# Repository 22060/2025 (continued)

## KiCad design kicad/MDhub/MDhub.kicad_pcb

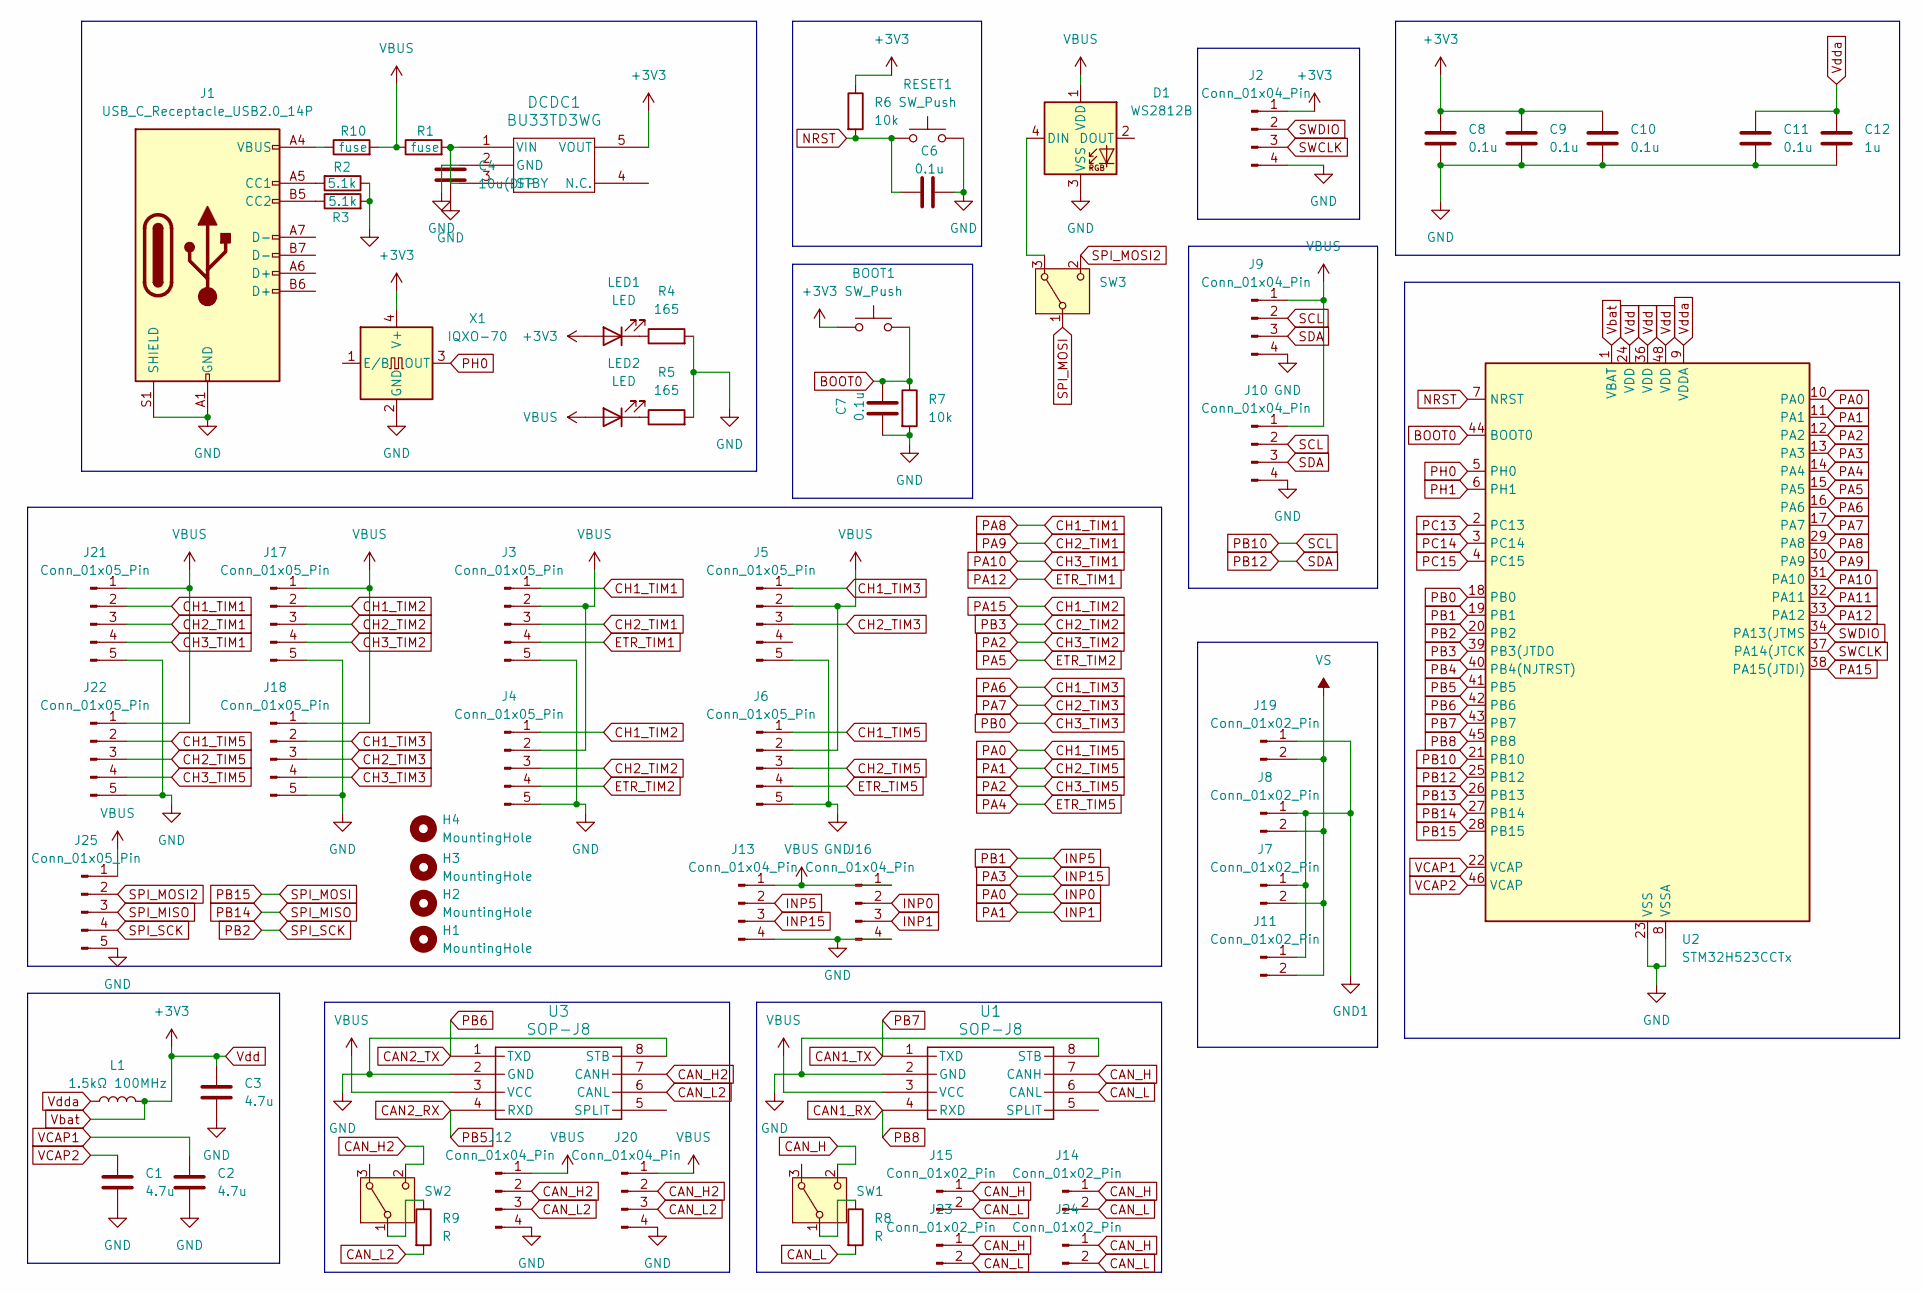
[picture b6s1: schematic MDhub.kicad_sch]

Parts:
BOOT1: SW_Push; SW_Tactile_SPST_NO_Straight_CK_PTS636Sx25SMTRLFS
C1, C2, C3: 4.7u; C_0603_1608Metric
C4: 10u(DFP; C_0603_1608Metric
C6, C7, C8, C9, C10, C11: 0.1u; C_0603_1608Metric
C12: 1u; C_0603_1608Metric
D1: WS2812B; LED_WS2812B_PLCC4_5.0x5.0mm_P3.2mm
DCDC1: BU33TD3WG; SSOP5
H1, H2, H3, H4: MountingHole; MountingHole_3.2mm_M3
J1: USB_C_Receptacle_USB2.0_14P; USB_C_Receptacle_aitendo
J2, J9, J10: Conn_01x04_Pin; Molex_KK-254_AE-6410-04A_1x04_P2.54mm_Vertical
J3, J4, J5, J6, J17, J18, J21, J22, J25: Conn_01x05_Pin; Molex_KK-254_AE-6410-05A_1x05_P2.54mm_Vertical
J7, J8: Conn_01x02_Pin; AMASS_XT60-F_1x02_P7.20mm_Vertical
J11, J19: Conn_01x02_Pin; AMASS_XT30PW-M_1x02_P2.50mm_Horizontal+3D
J12, J20: Conn_01x04_Pin; PinHeader_1x04_P2.54mm_Horizontal
J13, J16: Conn_01x04_Pin; Hirose_DF13-04P-1.25DSA_1x04_P1.25mm_Vertical
J14, J15, J23, J24: Conn_01x02_Pin; Hirose_DF13-02P-1.25DS_1x02_P1.25mm_Horizontal
L1: 1.5kΩ 100MHz; L_0805_2012Metric_Pad1.05x1.20mm_HandSolder
LED1, LED2: LED; LED_0603_1608Metric_Pad1.05x0.95mm_HandSolder
R1, R10: fuse; R_0603_1608Metric_Pad0.98x0.95mm_HandSolder
R2, R3: 5.1k; R_0603_1608Metric_Pad0.98x0.95mm_HandSolder
R4, R5: 165; R_0603_1608Metric_Pad0.98x0.95mm_HandSolder
R6, R7: 10k; R_0603_1608Metric_Pad0.98x0.95mm_HandSolder
R8, R9: R; R_0603_1608Metric_Pad0.98x0.95mm_HandSolder
RESET1: SW_Push; SW_Tactile_SPST_NO_Straight_CK_PTS636Sx25SMTRLFS
SW1, SW2, SW3: SW_Wuerth_450301014042; SW_Slide-03_Wuerth-WS-SLTV_10x2.5x6.4_P2.54mm
U1, U3: SOP-J8
U2: STM32H523CCTx; LQFP-48_7x7mm_P0.5mm
X1: IQXO-70; Oscillator_SMD_IQD_IQXO70-4Pin_7.5x5.0mm

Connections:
BOOT0: BOOT1.2, C7.2, R7.1, U2.44 (BOOT0)
CAN1_RX: U1.4 (RXD), U2.45 (PB8)
CAN1_TX: U1.1 (TXD), U2.43 (PB7)
CAN2_RX: U2.41 (PB5), U3.4 (RXD)
CAN2_TX: U2.42 (PB6), U3.1 (TXD)
CAN_H: J14.1, J15.1, J23.1, J24.1, SW1.2 (C), U1.7 (CANH)
CAN_H2: J12.2, J20.2, SW2.2 (C), U3.7 (CANH)
CAN_L: J14.2, J15.2, J23.2, J24.2, R8.2, U1.6 (CANL)
CAN_L2: J12.3, J20.3, R9.2, U3.6 (CANL)
CH1_TIM1: J3.1, J21.2, U2.29 (PA8)
CH1_TIM2: J4.1, J17.2, U2.38 (PA15(JTDI))
CH1_TIM3: J5.1, J18.2, U2.16 (PA6)
CH1_TIM5: J6.1, J16.2, J22.2, U2.10 (PA0)
CH2_TIM1: J3.3, J21.3, U2.30 (PA9)
CH2_TIM2: J4.3, J17.3, U2.39 (PB3(JTDO)
CH2_TIM3: J5.3, J18.3, U2.17 (PA7)
CH2_TIM5: J6.3, J16.3, J22.3, U2.11 (PA1)
CH3_TIM1: J21.4, U2.31 (PA10)
CH3_TIM2: J17.4, J22.4, U2.12 (PA2)
CH3_TIM3: J18.4, U2.18 (PB0)
ETR_TIM1: J3.4, U2.33 (PA12)
ETR_TIM2: J4.4, U2.15 (PA5)
ETR_TIM5: J6.4, U2.14 (PA4)
GND: C1.2, C2.2, C3.2, C4.2, C6.2, C7.1, C8.2, C9.2, C10.2, C11.2, C12.2, D1.3 (VSS), DCDC1.2 (GND), J1.A1 (GND), J1.A12 (GND), J1.B1 (GND), J1.B12 (GND), J1.S1 (SHIELD), J2.4, J3.5, J4.5, J5.5, J6.5, J9.4, J10.4, J12.4, J13.4, J16.4, J17.5, J18.5, J20.4, J21.5, J22.5, J25.5, R2.1, R3.2, R4.2, R5.2, R7.2, RESET1.2, U1.2 (GND), U1.8 (STB), U2.8 (VSSA), U2.23 (VSS), U2.35 (VSS), U2.47 (VSS), U3.2 (GND), U3.8 (STB), X1.2 (GND)
GND1: J7.1, J8.1, J11.1, J19.1
INP5: J13.2, U2.19 (PB1)
INP15: J13.3, U2.13 (PA3)
NRST: C6.1, R6.2, RESET1.1, U2.7 (NRST)
unnamed: D1.4 (DIN), SW3.3 (A)
unnamed: C4.1, DCDC1.1 (VIN), DCDC1.3 (STBY), R1.2
unnamed: J1.A5 (CC1), R2.2
unnamed: J1.B5 (CC2), R3.1
unnamed: J1.A4 (VBUS), J1.A9 (VBUS), J1.B4 (VBUS), J1.B9 (VBUS), R10.1
unnamed: LED1.1 (K), R4.1
unnamed: LED2.1 (K), R5.1
unnamed: R8.1, SW1.1 (B)
unnamed: R9.1, SW2.1 (B)
PA11: U2.32 (PA11)
PB2: J25.4, U2.20 (PB2)
PB4: U2.40 (PB4(NJTRST))
PB10: J9.2, J10.2, U2.21 (PB10)
PB12: J9.3, J10.3, U2.25 (PB12)
PB13: U2.26 (PB13)
PB14: J25.3, U2.27 (PB14)
PB15: SW3.1 (B), U2.28 (PB15)
PC13: U2.2 (PC13)
PC14: U2.3 (PC14)
PC15: U2.4 (PC15)
PH0: U2.5 (PH0), X1.3 (OUT)
PH1: U2.6 (PH1)
SPI_MOSI2: J25.2, SW3.2 (C)
SWCLK: J2.3, U2.37 (PA14(JTCK)
SWDIO: J2.2, U2.34 (PA13(JTMS)
VBUS: D1.1 (VDD), J3.2, J4.2, J5.2, J6.2, J9.1, J10.1, J12.1, J13.1, J16.1, J17.1, J18.1, J20.1, J21.1, J22.1, J25.1, LED2.2 (A), R1.1, R10.2, U1.3 (VCC), U3.3 (VCC)
VCAP1: C2.1, U2.22 (VCAP)
VCAP2: C1.1, U2.46 (VCAP)
VS: J7.2, J8.2, J11.2, J19.2
Vbat: BOOT1.1, C3.1, C8.1, C9.1, C10.1, DCDC1.5 (VOUT), J2.1, L1.2, LED1.2 (A), R6.1, U2.1 (VBAT), U2.24 (VDD), U2.36 (VDD), U2.48 (VDD), X1.4 (V+)
Vdda: C11.1, C12.1, L1.1, U2.9 (VDDA)

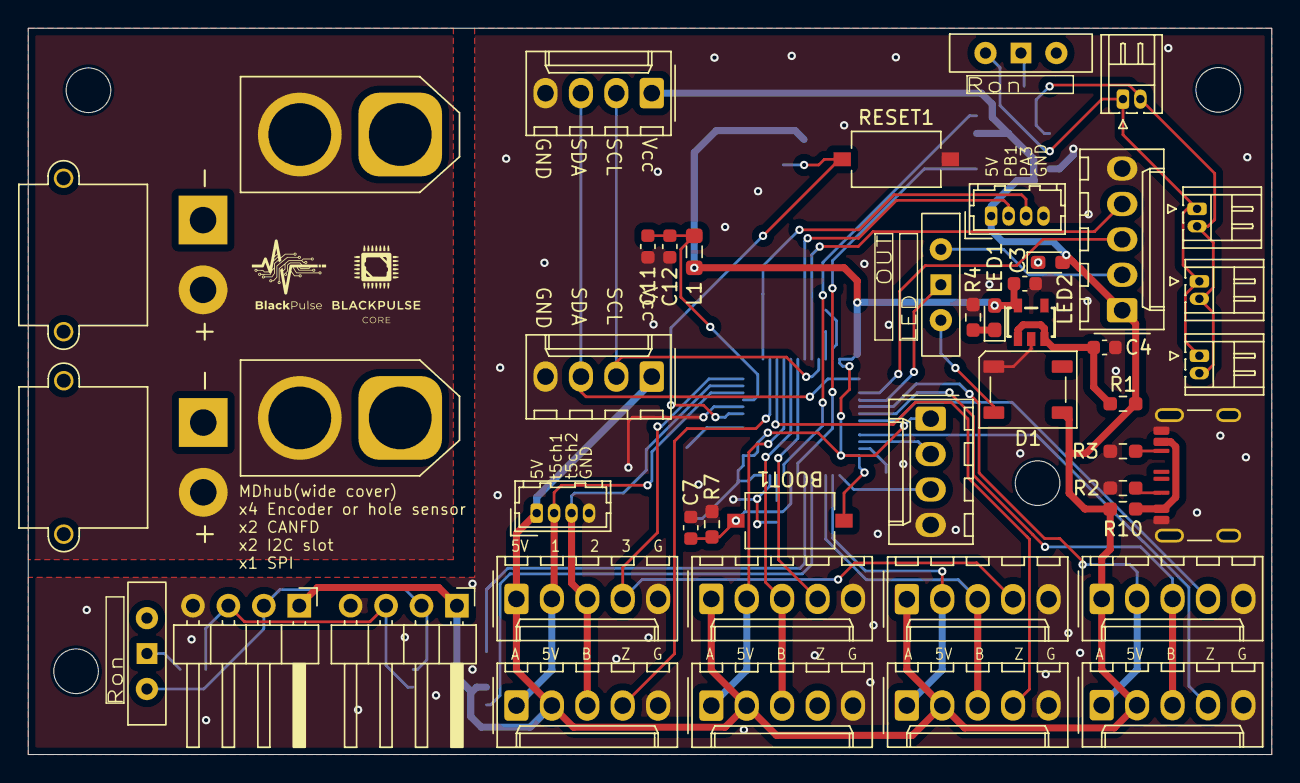
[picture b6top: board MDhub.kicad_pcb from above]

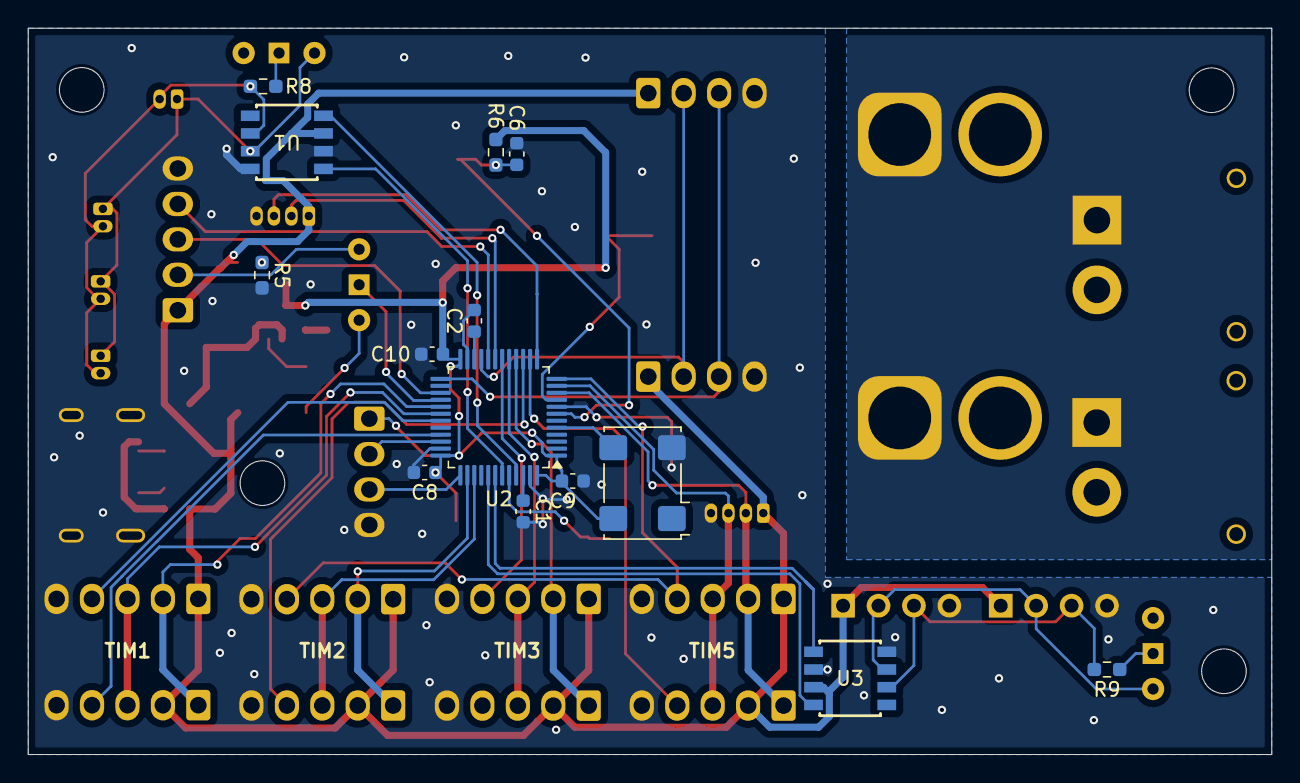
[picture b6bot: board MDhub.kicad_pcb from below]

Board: 2 copper layers, 89.2 x 52.1 mm, 64 parts (14 on the bottom side), 52 nets.

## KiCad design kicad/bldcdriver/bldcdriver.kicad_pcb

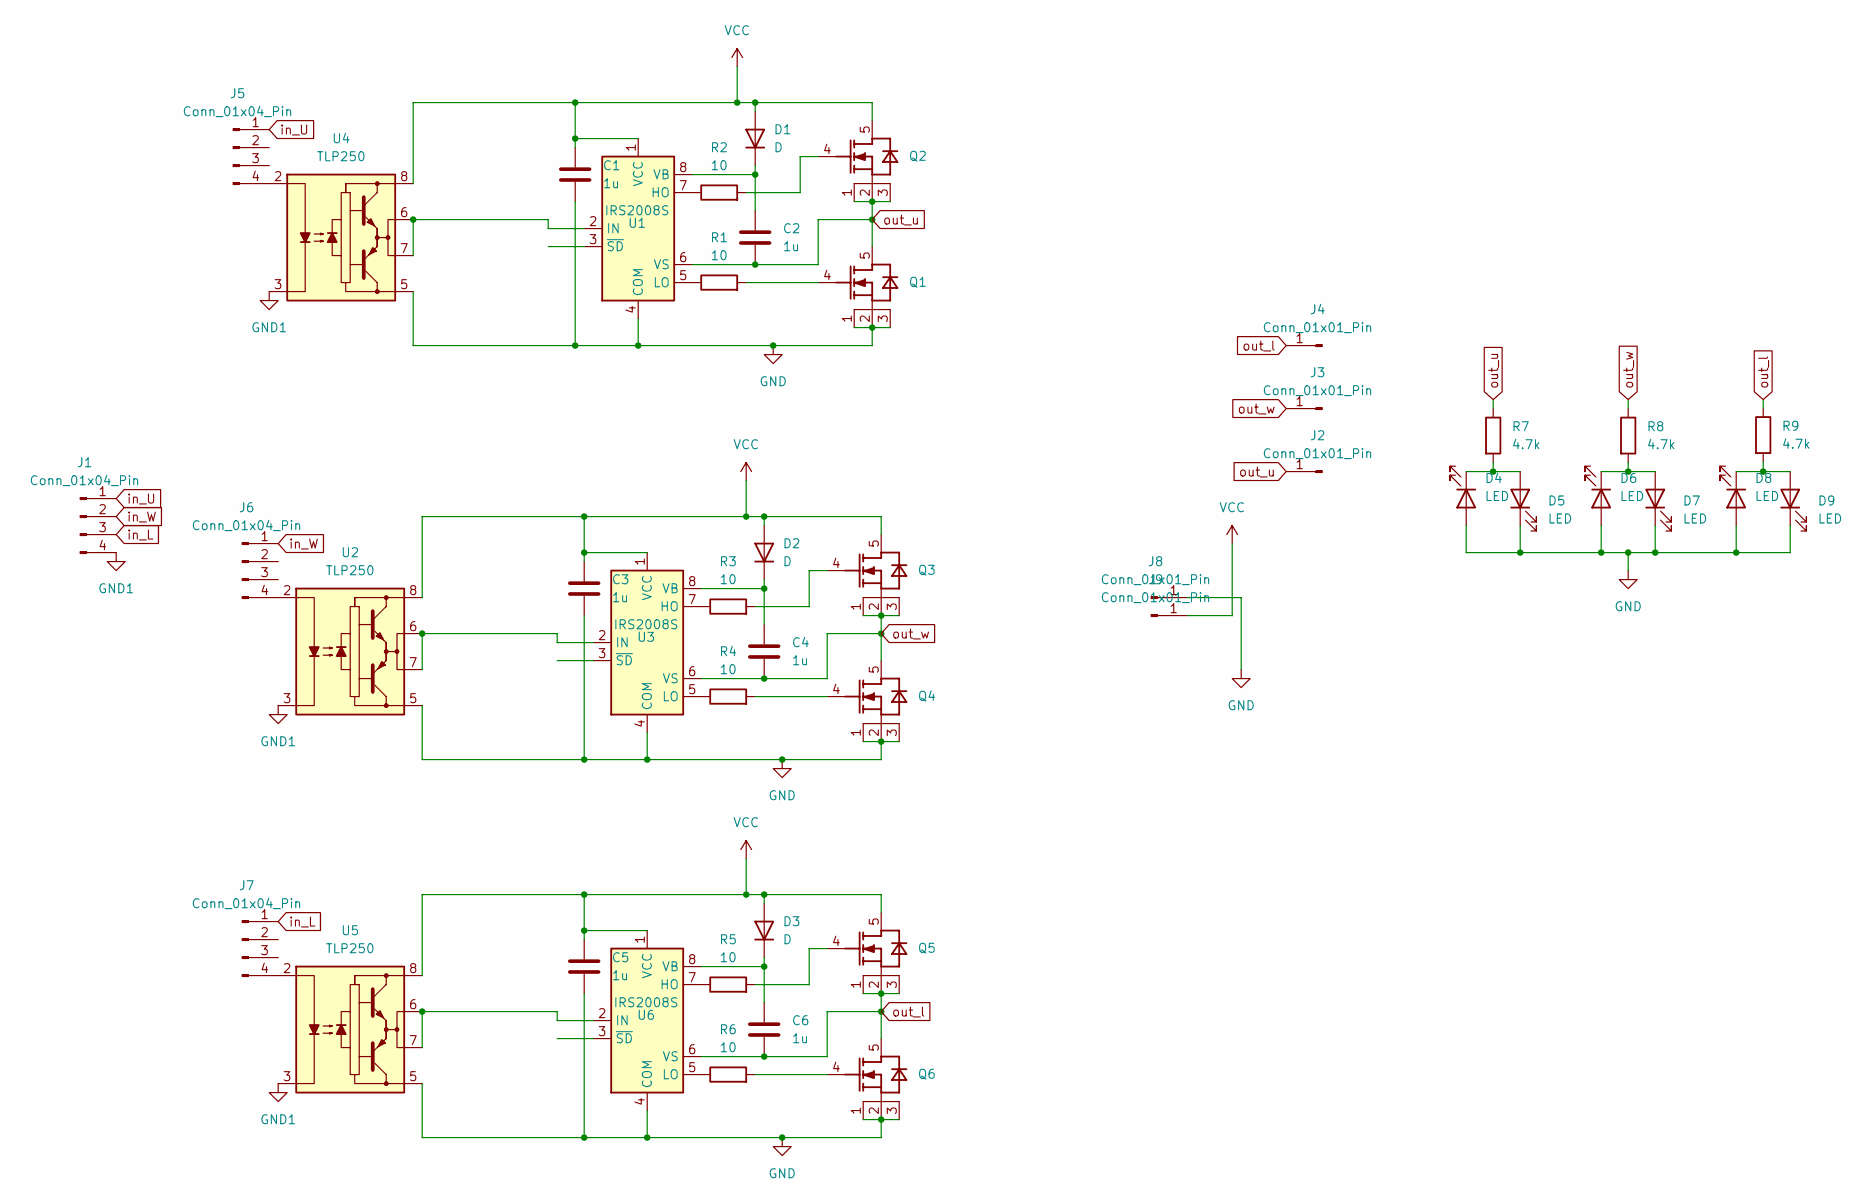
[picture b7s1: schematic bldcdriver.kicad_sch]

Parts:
C1, C2, C3, C4, C5, C6: 1u; C_0603_1608Metric
D1, D2, D3: D; D_0603_1608Metric
D4, D5, D6, D7, D8, D9: LED; LED_0603_1608Metric
J1: Conn_01x04_Pin; Molex_KK-254_AE-6410-04A_1x04_P2.54mm_Vertical
J2, J3, J4, J8, J9: Conn_01x01_Pin; bldc_connector
J5, J6, J7: Conn_01x04_Pin; PinHeader_1x04_P2.54mm_Vertical
Q1, Q2, Q3, Q4, Q5, Q6: RS6L120BGTB1
R1, R2, R3, R4, R5, R6: 10; R_0603_1608Metric_Pad0.98x0.95mm_HandSolder
R7, R8, R9: 4.7k; R_0603_1608Metric_Pad0.98x0.95mm_HandSolder
U1, U3, U6: IRS2008S; SOIC-8_3.9x4.9mm_P1.27mm
U2, U4, U5: TLP250; DIP-8_W7.62mm

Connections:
GND: C1.2, C3.2, C5.2, D4.2 (A), D5.1 (K), D6.2 (A), D7.1 (K), D8.2 (A), D9.1 (K), J8.1, Q1.1 (DRAIN), Q1.2 (DRAIN), Q1.3 (DRAIN), Q4.1 (DRAIN), Q4.2 (DRAIN), Q4.3 (DRAIN), Q6.1 (DRAIN), Q6.2 (DRAIN), Q6.3 (DRAIN), U1.4 (COM), U2.5 (VEE), U3.4 (COM), U4.5 (VEE), U5.5 (VEE), U6.4 (COM)
GND1: J1.4, U2.3 (C), U4.3 (C), U5.3 (C)
unnamed: C2.1, D1.1 (K), U1.8 (VB)
unnamed: C4.1, D2.1 (K), U3.8 (VB)
unnamed: C6.1, D3.1 (K), U6.8 (VB)
unnamed: D4.1 (K), D5.2 (A), R7.2
unnamed: D6.1 (K), D7.2 (A), R8.2
unnamed: D8.1 (K), D9.2 (A), R9.2
unnamed: J5.4, U4.2 (A)
unnamed: J6.4, U2.2 (A)
unnamed: J7.4, U5.2 (A)
unnamed: Q1.4 (GATE), R1.2
unnamed: Q2.4 (GATE), R2.2
unnamed: Q3.4 (GATE), R3.2
unnamed: Q4.4 (GATE), R4.2
unnamed: Q5.4 (GATE), R5.2
unnamed: Q6.4 (GATE), R6.2
unnamed: R2.1, U1.7 (HO)
unnamed: U1.2 (IN), U4.6 (VO), U4.7 (VO)
unnamed: R1.1, U1.5 (LO)
unnamed: R3.1, U3.7 (HO)
unnamed: U2.6 (VO), U2.7 (VO), U3.2 (IN)
unnamed: R4.1, U3.5 (LO)
unnamed: R5.1, U6.7 (HO)
unnamed: U5.6 (VO), U5.7 (VO), U6.2 (IN)
unnamed: R6.1, U6.5 (LO)
VCC: C1.1, C3.1, C5.1, D1.2 (A), D2.2 (A), D3.2 (A), J9.1, Q2.5 (DRAIN), Q3.5 (DRAIN), Q5.5 (DRAIN), U1.1 (VCC), U2.8 (VCC), U3.1 (VCC), U4.8 (VCC), U5.8 (VCC), U6.1 (VCC)
in_L: J1.3, J7.1
in_U: J1.1, J5.1
in_W: J1.2, J6.1
out_l: C6.2, J4.1, Q5.1 (DRAIN), Q5.2 (DRAIN), Q5.3 (DRAIN), Q6.5 (DRAIN), R9.1, U6.6 (VS)
out_u: C2.2, J2.1, Q1.5 (DRAIN), Q2.1 (DRAIN), Q2.2 (DRAIN), Q2.3 (DRAIN), R7.1, U1.6 (VS)
out_w: C4.2, J3.1, Q3.1 (DRAIN), Q3.2 (DRAIN), Q3.3 (DRAIN), Q4.5 (DRAIN), R8.1, U3.6 (VS)

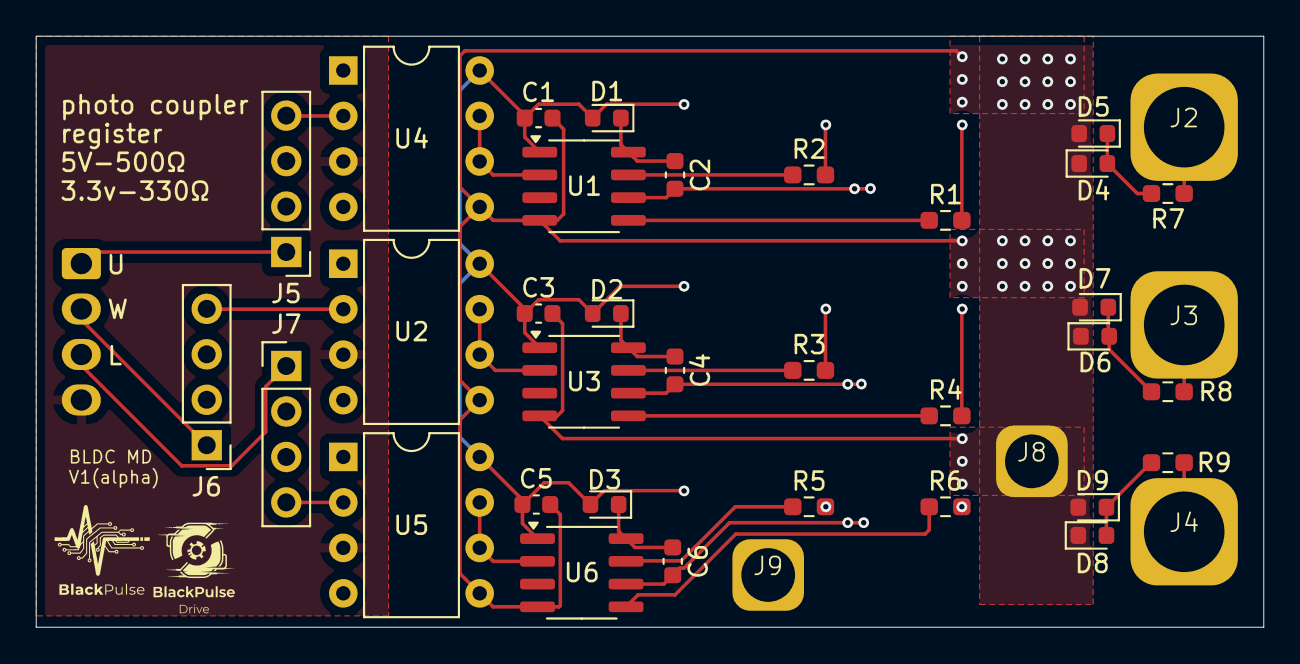
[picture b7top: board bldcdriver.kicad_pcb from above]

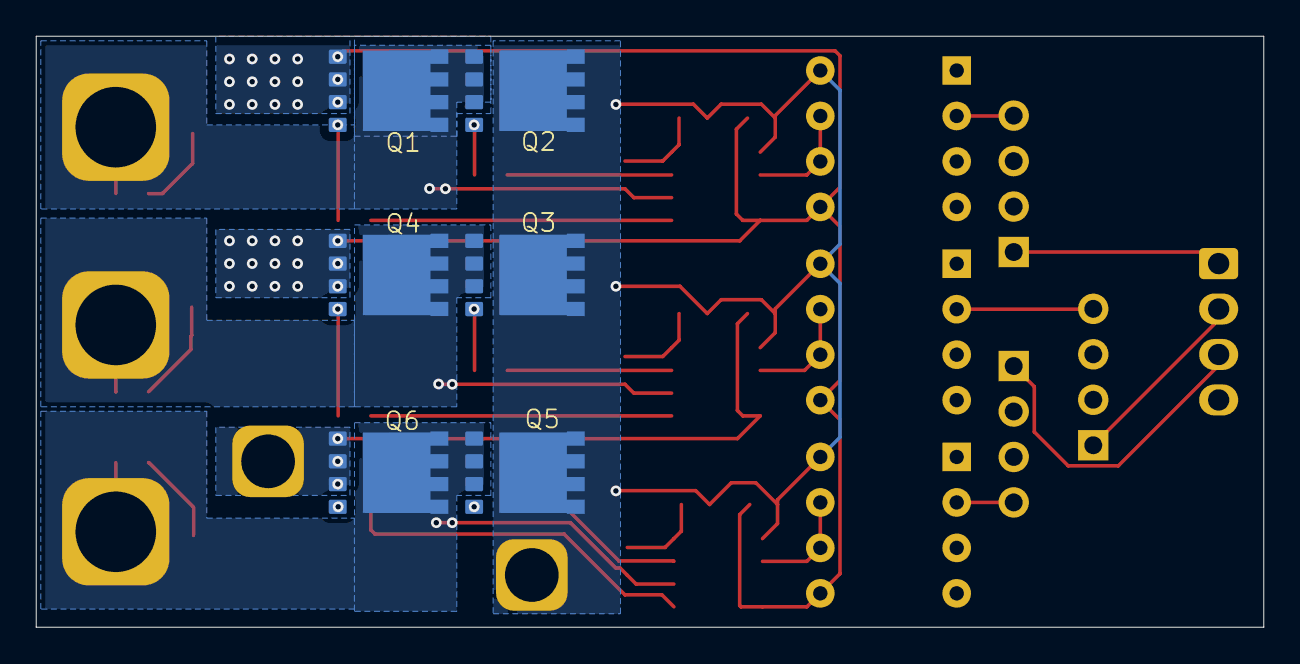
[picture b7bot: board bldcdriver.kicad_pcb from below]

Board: 2 copper layers, 68.6 x 33.0 mm, 45 parts (6 on the bottom side), 33 nets.

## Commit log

2025-06-18 add kicad folder
2025-06-18 add kicad folders to kicad folder
2025-06-19 perf MDhub circuit
2025-06-29 send to desktop
2025-06-30 finish
2025-07-01 mdhub
2025-07-02 hattyuuzumi
2025-08-26 test
2025-10-16 update commit id of submodule
2025-10-23 update submodule refs
